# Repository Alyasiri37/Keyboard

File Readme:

This is a custom mechanical keyboard projects that is still under development. This is the PCB design for the keyboard.

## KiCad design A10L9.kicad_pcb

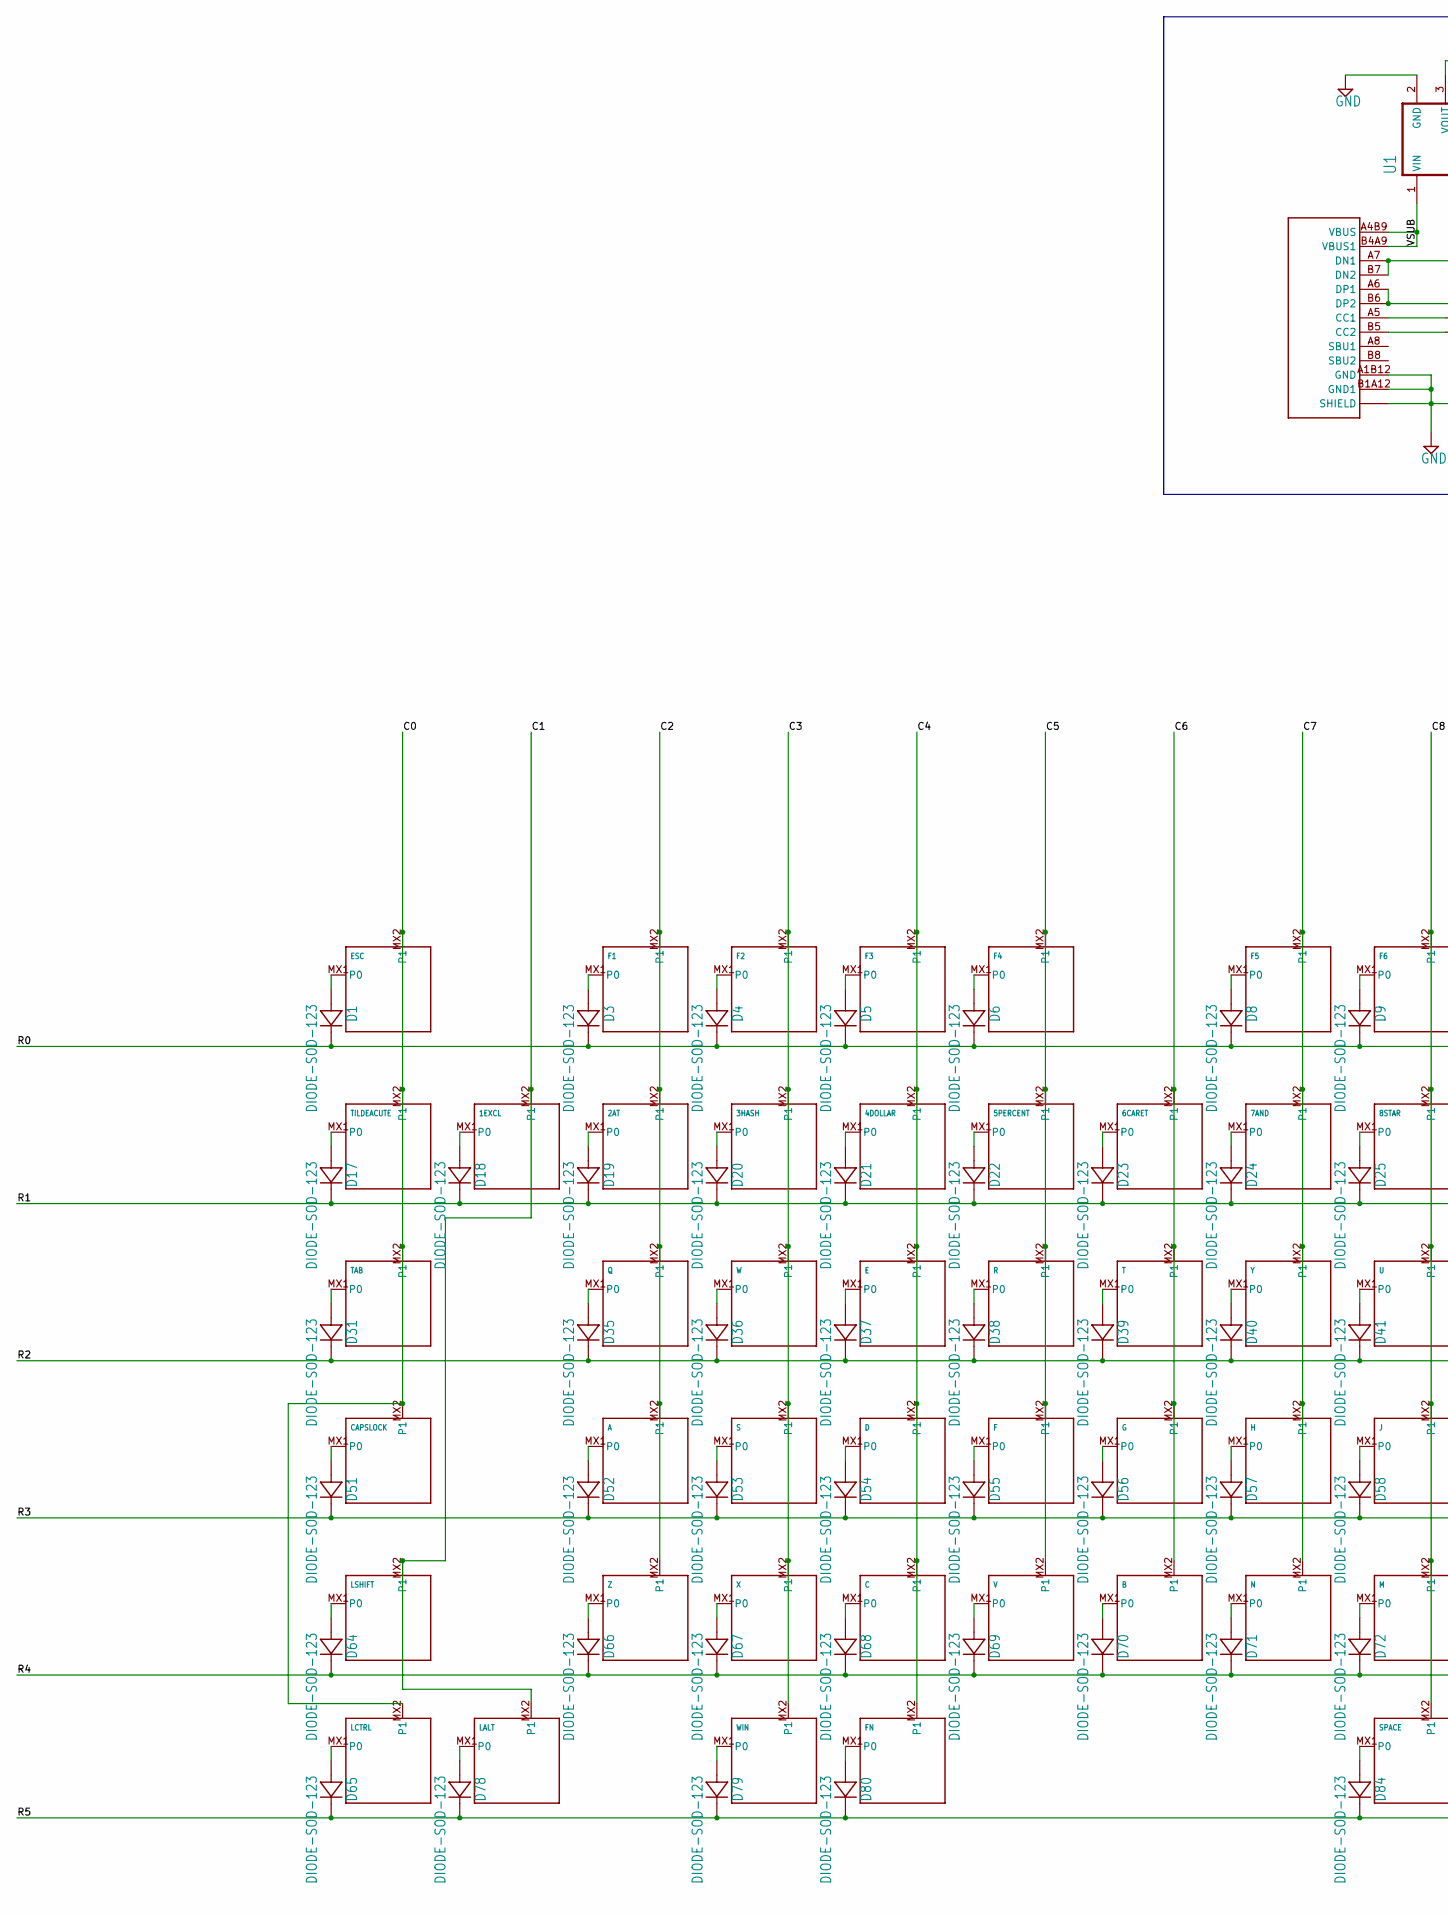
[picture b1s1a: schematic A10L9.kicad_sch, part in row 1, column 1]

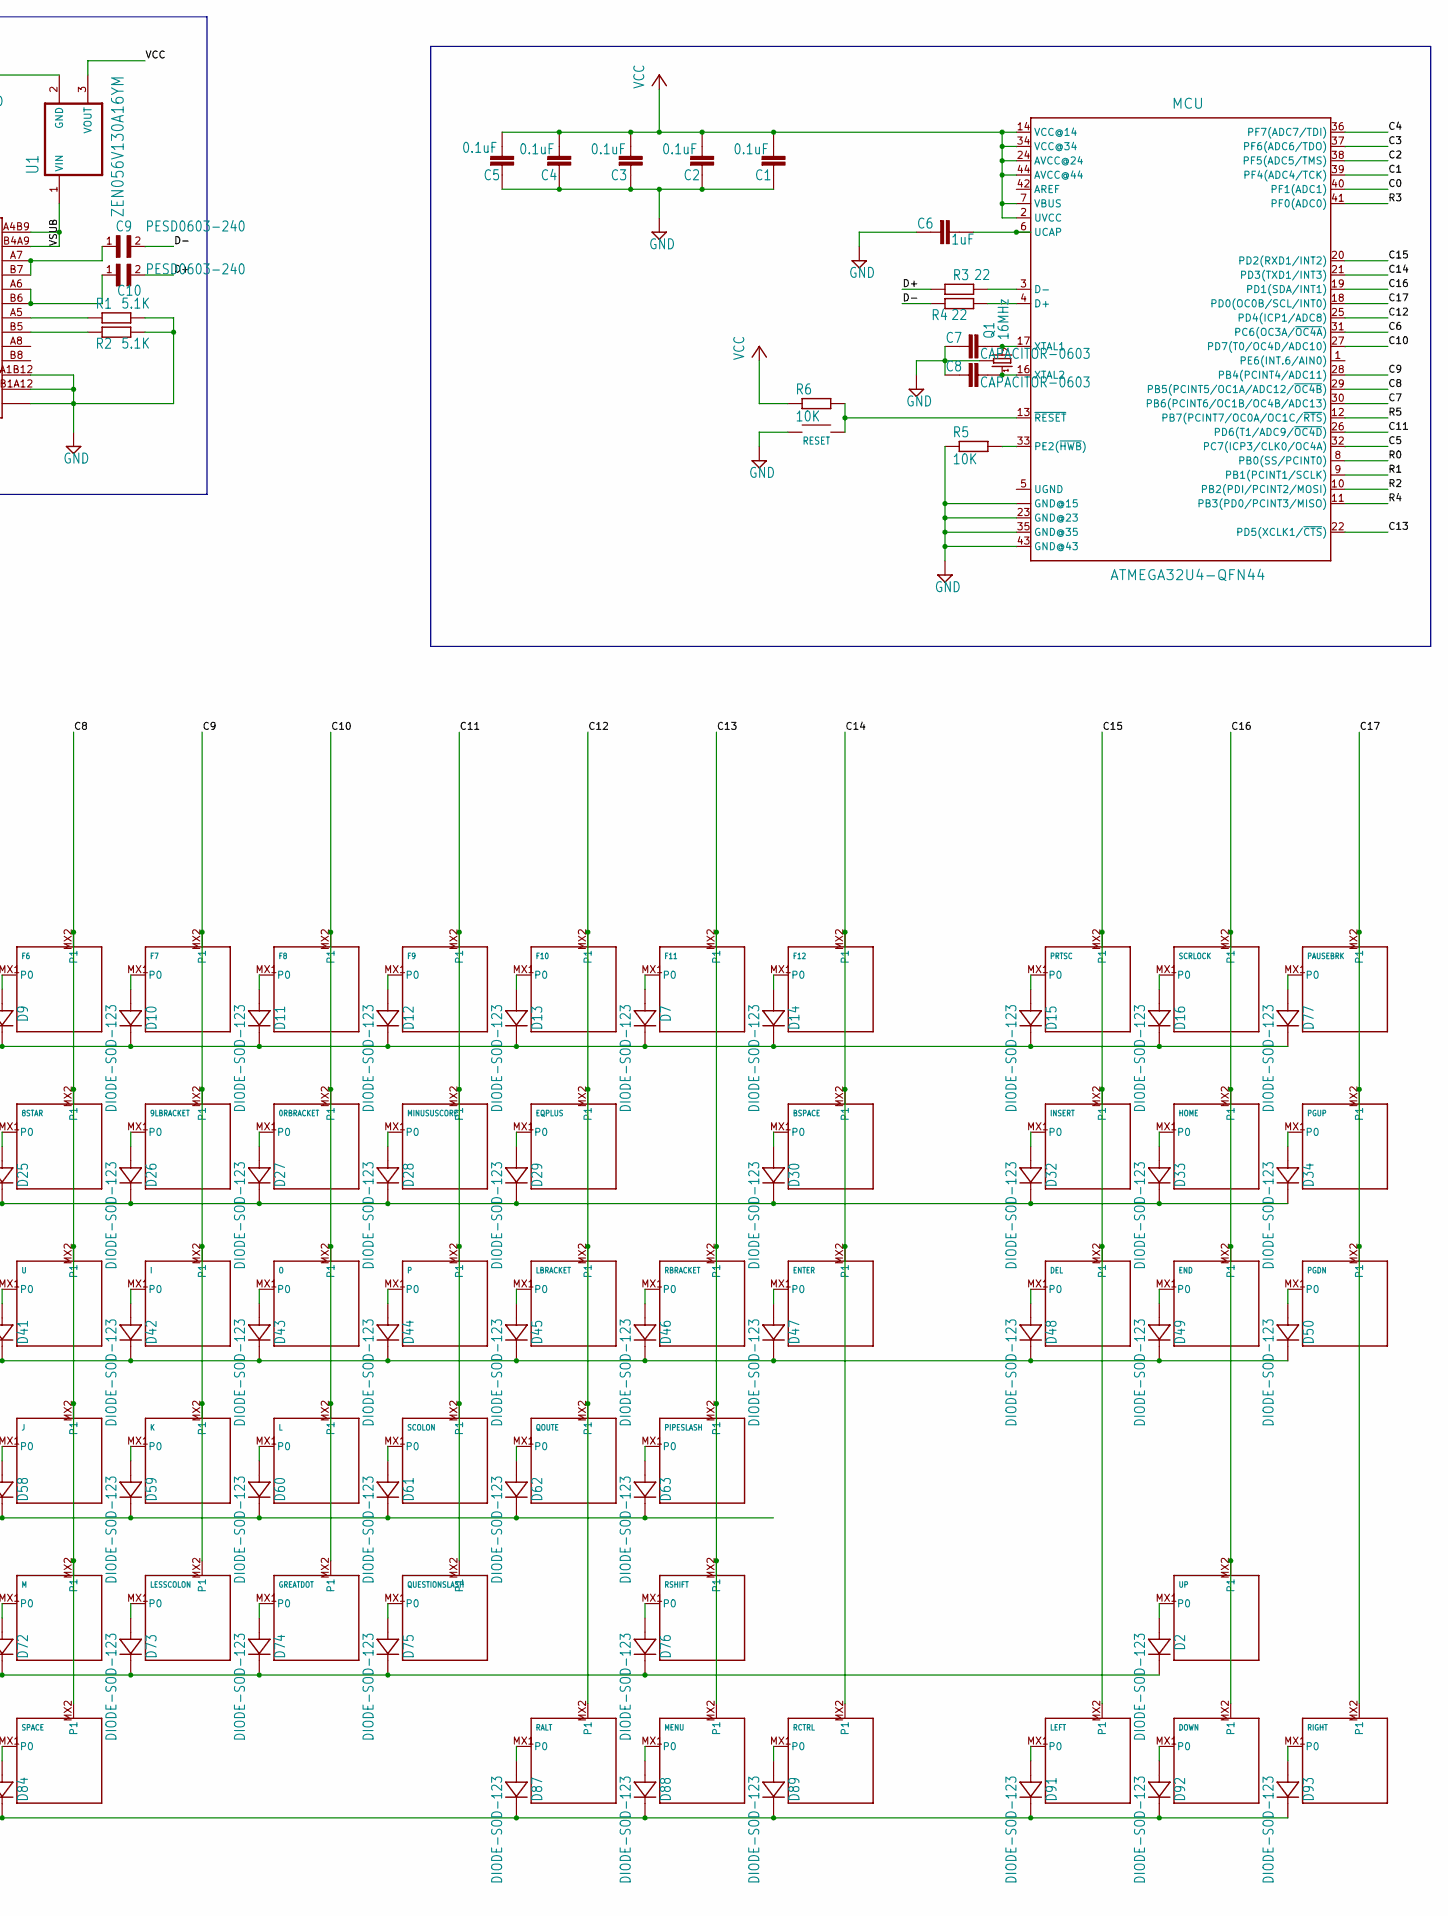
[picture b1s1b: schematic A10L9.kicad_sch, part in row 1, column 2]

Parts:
0RBRACKET, 1EXCL, 2AT, 3HASH, 4DOLLAR, 5PERCENT, 6CARET, 7AND, 8STAR, 9LBRACKET: KEYSWITCH-PLAIN-MX-1U; MX-1U
A: KEYSWITCH-PLAIN-MX-1U; MX-1U
B: KEYSWITCH-PLAIN-MX-1U; MX-1U
BSPACE: KEYSWITCH-PLAIN-MX-2U; MX-2U
C: KEYSWITCH-PLAIN-MX-1U; MX-1U
C1, C2, C3, C4, C5: 0.1uF; C0603
C6: 1uF; C0603
C7, C8: CAPACITOR-0603; C0603
C9, C10: PESD0603-240; DIONC1608X55N
CAPSLOCK: KEYSWITCH-PLAIN-MX-1U; MX-1U
D: KEYSWITCH-PLAIN-MX-1U; MX-1U
D1, D2, D3, D4, D5, D6, D7, D8, D9, D10, D11, D12, D13, D14, D15, D16, D17, D18, D19, D20, D21, D22, D23, D24, D25, D26, D27, D28, D29, D30, D31, D32, D33, D34, D35, D36, D37, D38, D39, D40, D41, D42, D43, D44, D45, D46, D47, D48, D49, D50, D51, D52, D53, D54, D55, D56, D57, D58, D59, D60, D61, D62, D63, D64, D65, D66, D67, D68, D69, D70, D71, D72, D73, D74, D75, D76, D77, D78, D79, D80, D84, D87, D88, D89, D91, D92, D93: DIODE-SOD-123; SOD-123
DEL: KEYSWITCH-PLAIN-MX-1U; MX-1U
DOWN: KEYSWITCH-PLAIN-MX-1U; MX-1U
E: KEYSWITCH-PLAIN-MX-1U; MX-1U
END: KEYSWITCH-PLAIN-MX-1U; MX-1U
ENTER: KEYSWITCH-PLAIN-MX-2U-ROTATED; MX-2U-ROTATED
EQPLUS: KEYSWITCH-PLAIN-MX-1U; MX-1U
ESC: KEYSWITCH-PLAIN-MX-1U; MX-1U
F, F1, F2, F3, F4, F5, F6, F7, F8, F9, F10, F11, F12: KEYSWITCH-PLAIN-MX-1U; MX-1U
FN: KEYSWITCH-PLAIN-MX-1U; MX-1U
G: KEYSWITCH-PLAIN-MX-1U; MX-1U
GREATDOT: KEYSWITCH-PLAIN-MX-1U; MX-1U
H: KEYSWITCH-PLAIN-MX-1U; MX-1U
HOME: KEYSWITCH-PLAIN-MX-1U; MX-1U
I: KEYSWITCH-PLAIN-MX-1U; MX-1U
INSERT: KEYSWITCH-PLAIN-MX-1U; MX-1U
J: KEYSWITCH-PLAIN-MX-1U; MX-1U
K: KEYSWITCH-PLAIN-MX-1U; MX-1U
L: KEYSWITCH-PLAIN-MX-1U; MX-1U
LALT: KEYSWITCH-PLAIN-MX-1U; MX-1U
LBRACKET: KEYSWITCH-PLAIN-MX-1U; MX-1U
LCTRL: KEYSWITCH-PLAIN-MX-1U; MX-1U
LEFT: KEYSWITCH-PLAIN-MX-1U; MX-1U
LESSCOLON: KEYSWITCH-PLAIN-MX-1U; MX-1U
LSHIFT: KEYSWITCH-PLAIN-MX-2U; MX-2U
M: KEYSWITCH-PLAIN-MX-1U; MX-1U
MCU: ATMEGA32U4-QFN44; QFN-44
MENU: KEYSWITCH-PLAIN-MX-1U; MX-1U
MINUSUSCORE: KEYSWITCH-PLAIN-MX-1U; MX-1U
N: KEYSWITCH-PLAIN-MX-1U; MX-1U
O: KEYSWITCH-PLAIN-MX-1U; MX-1U
P: KEYSWITCH-PLAIN-MX-1U; MX-1U
PAUSEBRK: KEYSWITCH-PLAIN-MX-1U; MX-1U
PGDN: KEYSWITCH-PLAIN-MX-1U; MX-1U
PGUP: KEYSWITCH-PLAIN-MX-1U; MX-1U
PIPESLASH: KEYSWITCH-PLAIN-MX-1U; MX-1U
PRTSC: KEYSWITCH-PLAIN-MX-1U; MX-1U
Q: KEYSWITCH-PLAIN-MX-1U; MX-1U
Q1: 16MHz; 2.0X1.6_KX-5
QOUTE: KEYSWITCH-PLAIN-MX-1U; MX-1U
QUESTIONSLASH: KEYSWITCH-PLAIN-MX-1U; MX-1U
R: KEYSWITCH-PLAIN-MX-1U; MX-1U
R1, R2: 5.1K; R0603
R3, R4: 22; R0603
R5, R6: 10K; R0603
RALT: KEYSWITCH-PLAIN-MX-1U; MX-1U
RBRACKET: KEYSWITCH-PLAIN-MX-1U; MX-1U
RCTRL: KEYSWITCH-PLAIN-MX-1U; MX-1U
RESET: SWITCH-SMD-EVP-BB2A9B00
RIGHT: KEYSWITCH-PLAIN-MX-1U; MX-1U
RSHIFT: KEYSWITCH-PLAIN-MX-2U; MX-2U
S: KEYSWITCH-PLAIN-MX-1U; MX-1U
SCOLON: KEYSWITCH-PLAIN-MX-1U; MX-1U
SCRLOCK: KEYSWITCH-PLAIN-MX-1U; MX-1U
SPACE: KEYSWITCH-PLAIN-MX-7U-FLIPPED; MX-7U-FLIPPED
T: KEYSWITCH-PLAIN-MX-1U; MX-1U
TAB: KEYSWITCH-PLAIN-MX-1U; MX-1U
TILDEACUTE: KEYSWITCH-PLAIN-MX-1U; MX-1U
U: KEYSWITCH-PLAIN-MX-1U; MX-1U
U1: ZEN056V130A16YM; TVS_ZEN056V260A16YC
U$1: USB-C
UP: KEYSWITCH-PLAIN-MX-1U; MX-1U
V: KEYSWITCH-PLAIN-MX-1U; MX-1U
W: KEYSWITCH-PLAIN-MX-1U; MX-1U
WIN: KEYSWITCH-PLAIN-MX-1U; MX-1U
X: KEYSWITCH-PLAIN-MX-1U; MX-1U
Y: KEYSWITCH-PLAIN-MX-1U; MX-1U
Z: KEYSWITCH-PLAIN-MX-1U; MX-1U

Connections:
C0: CAPSLOCK.MX2 (P1), ESC.MX2 (P1), LCTRL.MX2 (P1), MCU.40 (PF1(ADC1)), TAB.MX2 (P1), TILDEACUTE.MX2 (P1)
C1: 1EXCL.MX2 (P1), LALT.MX2 (P1), LSHIFT.MX2 (P1), MCU.39 (PF4(ADC4/TCK))
C2: 2AT.MX2 (P1), A.MX2 (P1), F1.MX2 (P1), MCU.38 (PF5(ADC5/TMS)), Q.MX2 (P1), Z.MX2 (P1)
C3: 3HASH.MX2 (P1), F2.MX2 (P1), MCU.37 (PF6(ADC6/TDO)), S.MX2 (P1), W.MX2 (P1), WIN.MX2 (P1), X.MX2 (P1)
C4: 4DOLLAR.MX2 (P1), C.MX2 (P1), D.MX2 (P1), E.MX2 (P1), F3.MX2 (P1), FN.MX2 (P1), MCU.36 (PF7(ADC7/TDI))
C5: 5PERCENT.MX2 (P1), F.MX2 (P1), F4.MX2 (P1), MCU.32 (PC7(ICP3/CLK0/OC4A)), R.MX2 (P1), V.MX2 (P1)
C6: 6CARET.MX2 (P1), B.MX2 (P1), G.MX2 (P1), MCU.31 (PC6(OC3A/~OC4A)), T.MX2 (P1)
C7: 7AND.MX2 (P1), F5.MX2 (P1), H.MX2 (P1), MCU.30 (PB6(PCINT6/OC1B/OC4B/ADC13)), N.MX2 (P1), Y.MX2 (P1)
C8: 8STAR.MX2 (P1), F6.MX2 (P1), J.MX2 (P1), M.MX2 (P1), MCU.29 (PB5(PCINT5/OC1A/ADC12/~OC4B)), SPACE.MX2 (P1), U.MX2 (P1)
C9: 9LBRACKET.MX2 (P1), F7.MX2 (P1), I.MX2 (P1), K.MX2 (P1), LESSCOLON.MX2 (P1), MCU.28 (PB4(PCINT4/ADC11))
C10: 0RBRACKET.MX2 (P1), F8.MX2 (P1), GREATDOT.MX2 (P1), L.MX2 (P1), MCU.27 (PD7(T0/OC4D/ADC10)), O.MX2 (P1)
C11: F9.MX2 (P1), MCU.26 (PD6(T1/ADC9/~OC4D)), MINUSUSCORE.MX2 (P1), P.MX2 (P1), QUESTIONSLASH.MX2 (P1), SCOLON.MX2 (P1)
C12: EQPLUS.MX2 (P1), F10.MX2 (P1), LBRACKET.MX2 (P1), MCU.25 (PD4(ICP1/ADC8)), QOUTE.MX2 (P1), RALT.MX2 (P1)
C13: F11.MX2 (P1), MCU.22 (PD5(XCLK1/~CTS)), MENU.MX2 (P1), PIPESLASH.MX2 (P1), RBRACKET.MX2 (P1), RSHIFT.MX2 (P1)
C14: BSPACE.MX2 (P1), ENTER.MX2 (P1), F12.MX2 (P1), MCU.21 (PD3(TXD1/INT3)), RCTRL.MX2 (P1)
C15: DEL.MX2 (P1), INSERT.MX2 (P1), LEFT.MX2 (P1), MCU.20 (PD2(RXD1/INT2)), PRTSC.MX2 (P1)
C16: DOWN.MX2 (P1), END.MX2 (P1), HOME.MX2 (P1), MCU.19 (PD1(SDA/INT1)), SCRLOCK.MX2 (P1), UP.MX2 (P1)
C17: MCU.18 (PD0(OC0B/SCL/INT0)), PAUSEBRK.MX2 (P1), PGDN.MX2 (P1), PGUP.MX2 (P1), RIGHT.MX2 (P1)
D+: C10.2, R3.1
D-: C9.2, R4.1
GND: C1.1, C2.1, C3.1, C4.1, C5.1, C6.1, C7.1, C8.1, MCU.15 (GND@15), MCU.23 (GND@23), MCU.35 (GND@35), MCU.43 (GND@43), MCU.TAB (GND@15), Q1.2 (3), Q1.4 (3), R1.2, R2.2, R5.1, RESET.A@1 (1), RESET.A@2 (1), U1.2 (GND), U$1.A1B12 (GND), U$1.B1A12 (GND1), U$1.P$13 (SHIELD), U$1.P$14 (SHIELD), U$1.P$15 (SHIELD), U$1.P$16 (SHIELD)
unnamed: D1.A, ESC.MX1 (P0)
unnamed: D3.A, F1.MX1 (P0)
unnamed: D4.A, F2.MX1 (P0)
unnamed: D5.A, F3.MX1 (P0)
unnamed: D6.A, F4.MX1 (P0)
unnamed: D7.A, F11.MX1 (P0)
unnamed: D8.A, F5.MX1 (P0)
unnamed: D9.A, F6.MX1 (P0)
unnamed: D10.A, F7.MX1 (P0)
unnamed: D11.A, F8.MX1 (P0)
unnamed: D12.A, F9.MX1 (P0)
unnamed: D13.A, F10.MX1 (P0)
unnamed: D14.A, F12.MX1 (P0)
unnamed: D15.A, PRTSC.MX1 (P0)
unnamed: D16.A, SCRLOCK.MX1 (P0)
unnamed: D77.A, PAUSEBRK.MX1 (P0)
unnamed: D17.A, TILDEACUTE.MX1 (P0)
unnamed: 1EXCL.MX1 (P0), D18.A
unnamed: 2AT.MX1 (P0), D19.A
unnamed: 3HASH.MX1 (P0), D20.A
unnamed: 4DOLLAR.MX1 (P0), D21.A
unnamed: 5PERCENT.MX1 (P0), D22.A
unnamed: 6CARET.MX1 (P0), D23.A
unnamed: 7AND.MX1 (P0), D24.A
unnamed: 8STAR.MX1 (P0), D25.A
unnamed: 9LBRACKET.MX1 (P0), D26.A
unnamed: 0RBRACKET.MX1 (P0), D27.A
unnamed: D28.A, MINUSUSCORE.MX1 (P0)
unnamed: D29.A, EQPLUS.MX1 (P0)
unnamed: BSPACE.MX1 (P0), D30.A
unnamed: D32.A, INSERT.MX1 (P0)
unnamed: D33.A, HOME.MX1 (P0)
unnamed: D34.A, PGUP.MX1 (P0)
unnamed: D31.A, TAB.MX1 (P0)
unnamed: D35.A, Q.MX1 (P0)
unnamed: D36.A, W.MX1 (P0)
unnamed: D37.A, E.MX1 (P0)
unnamed: D38.A, R.MX1 (P0)
unnamed: D39.A, T.MX1 (P0)
unnamed: D40.A, Y.MX1 (P0)
unnamed: D41.A, U.MX1 (P0)
unnamed: D42.A, I.MX1 (P0)
unnamed: D43.A, O.MX1 (P0)
unnamed: D44.A, P.MX1 (P0)
unnamed: D45.A, LBRACKET.MX1 (P0)
unnamed: D46.A, RBRACKET.MX1 (P0)
unnamed: D47.A, ENTER.MX1 (P0)
unnamed: D48.A, DEL.MX1 (P0)
unnamed: D49.A, END.MX1 (P0)
unnamed: D50.A, PGDN.MX1 (P0)
unnamed: CAPSLOCK.MX1 (P0), D51.A
unnamed: A.MX1 (P0), D52.A
unnamed: D53.A, S.MX1 (P0)
unnamed: D.MX1 (P0), D54.A
unnamed: D55.A, F.MX1 (P0)
unnamed: D56.A, G.MX1 (P0)
unnamed: D57.A, H.MX1 (P0)
unnamed: D58.A, J.MX1 (P0)
unnamed: D59.A, K.MX1 (P0)
unnamed: D60.A, L.MX1 (P0)
unnamed: D61.A, SCOLON.MX1 (P0)
unnamed: D62.A, QOUTE.MX1 (P0)
unnamed: D63.A, PIPESLASH.MX1 (P0)
unnamed: D64.A, LSHIFT.MX1 (P0)
unnamed: D66.A, Z.MX1 (P0)
unnamed: D67.A, X.MX1 (P0)
unnamed: C.MX1 (P0), D68.A
unnamed: D69.A, V.MX1 (P0)
unnamed: B.MX1 (P0), D70.A
unnamed: D71.A, N.MX1 (P0)
unnamed: D72.A, M.MX1 (P0)
unnamed: D73.A, LESSCOLON.MX1 (P0)
unnamed: D74.A, GREATDOT.MX1 (P0)
unnamed: D75.A, QUESTIONSLASH.MX1 (P0)
unnamed: D76.A, RSHIFT.MX1 (P0)
unnamed: D2.A, UP.MX1 (P0)
unnamed: D87.A, RALT.MX1 (P0)
unnamed: D88.A, MENU.MX1 (P0)
unnamed: D89.A, RCTRL.MX1 (P0)
unnamed: D91.A, LEFT.MX1 (P0)
unnamed: D92.A, DOWN.MX1 (P0)
unnamed: D93.A, RIGHT.MX1 (P0)
unnamed: D84.A, SPACE.MX1 (P0)
unnamed: D65.A, LCTRL.MX1 (P0)
unnamed: D78.A, LALT.MX1 (P0)
unnamed: D79.A, WIN.MX1 (P0)
unnamed: D80.A, FN.MX1 (P0)
unnamed: C9.1, U$1.A7 (DN1), U$1.B7 (DN2)
unnamed: R1.1, U$1.A5 (CC1)
unnamed: R2.1, U$1.B5 (CC2)
unnamed: MCU.3 (D-), R3.2
unnamed: C6.2, MCU.6 (UCAP)
unnamed: MCU.4 (D+), R4.2
unnamed: MCU.33 (PE2(~HWB)), R5.2
unnamed: C10.1, U$1.A6 (DP1), U$1.B6 (DP2)
unnamed: C7.2, MCU.17 (XTAL1), Q1.3 (2)
unnamed: C8.2, MCU.16 (XTAL2), Q1.1
unnamed: MCU.13 (~RESET), R6.2, RESET.B@3 (2), RESET.B@4 (2)
R0: D1.C, D3.C, D4.C, D5.C, D6.C, D7.C, D8.C, D9.C, D10.C, D11.C, D12.C, D13.C, D14.C, D15.C, D16.C, D77.C, MCU.8 (PB0(SS/PCINT0))
R1: D17.C, D18.C, D19.C, D20.C, D21.C, D22.C, D23.C, D24.C, D25.C, D26.C, D27.C, D28.C, D29.C, D30.C, D32.C, D33.C, D34.C, MCU.9 (PB1(PCINT1/SCLK))
R2: D31.C, D35.C, D36.C, D37.C, D38.C, D39.C, D40.C, D41.C, D42.C, D43.C, D44.C, D45.C, D46.C, D47.C, D48.C, D49.C, D50.C, MCU.10 (PB2(PDI/PCINT2/MOSI))
R3: D51.C, D52.C, D53.C, D54.C, D55.C, D56.C, D57.C, D58.C, D59.C, D60.C, D61.C, D62.C, D63.C, MCU.41 (PF0(ADC0))
R4: D2.C, D64.C, D66.C, D67.C, D68.C, D69.C, D70.C, D71.C, D72.C, D73.C, D74.C, D75.C, D76.C, MCU.11 (PB3(PD0/PCINT3/MISO))
R5: D65.C, D78.C, D79.C, D80.C, D84.C, D87.C, D88.C, D89.C, D91.C, D92.C, D93.C, MCU.12 (PB7(PCINT7/OC0A/OC1C/~RTS))
VCC: C1.2, C2.2, C3.2, C4.2, C5.2, MCU.2 (UVCC), MCU.7 (VBUS), MCU.14 (VCC@14), MCU.24 (AVCC@24), MCU.34 (VCC@34), MCU.44 (AVCC@44), R6.1, U1.3 (VOUT)
VSUB: U1.1 (VIN), U$1.A4B9 (VBUS), U$1.B4A9 (VBUS1)

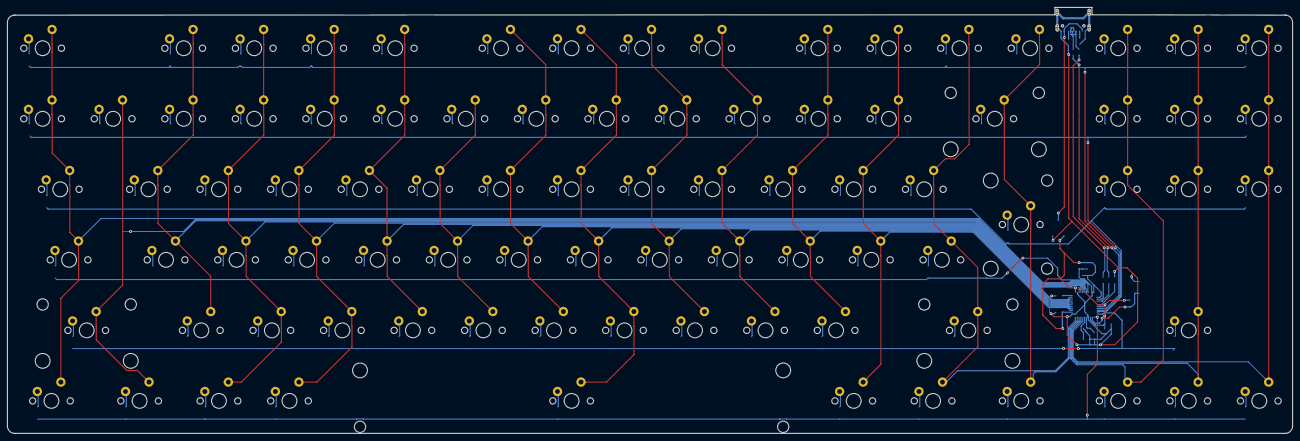
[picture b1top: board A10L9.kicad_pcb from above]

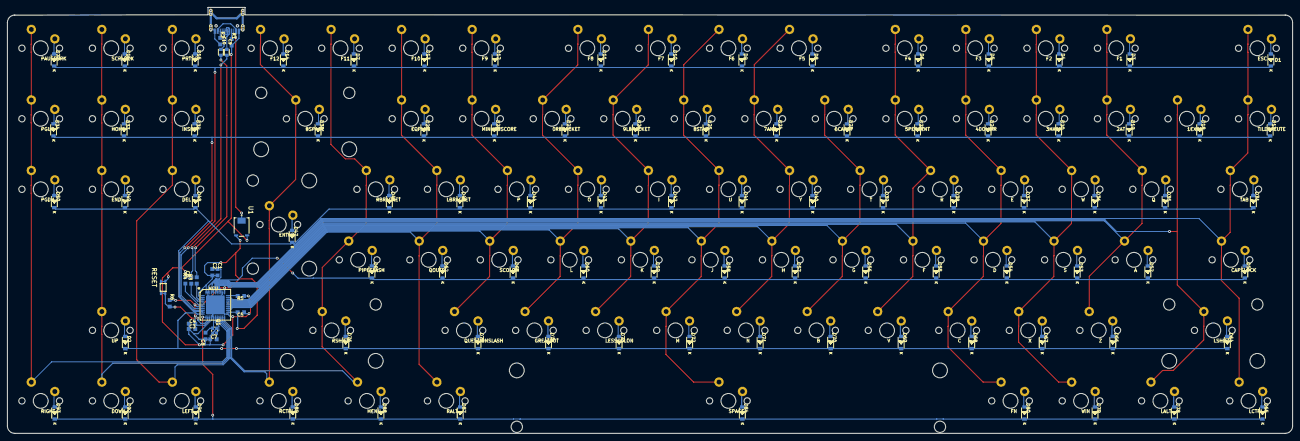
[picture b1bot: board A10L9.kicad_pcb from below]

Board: 2 copper layers, 347.1 x 115.0 mm, 195 parts (108 on the bottom side), 127 nets.
